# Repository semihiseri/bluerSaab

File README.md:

# bluerSaab
An ESP32 Port of the great BlueSaab projects. What? Yes, I lack creativity.

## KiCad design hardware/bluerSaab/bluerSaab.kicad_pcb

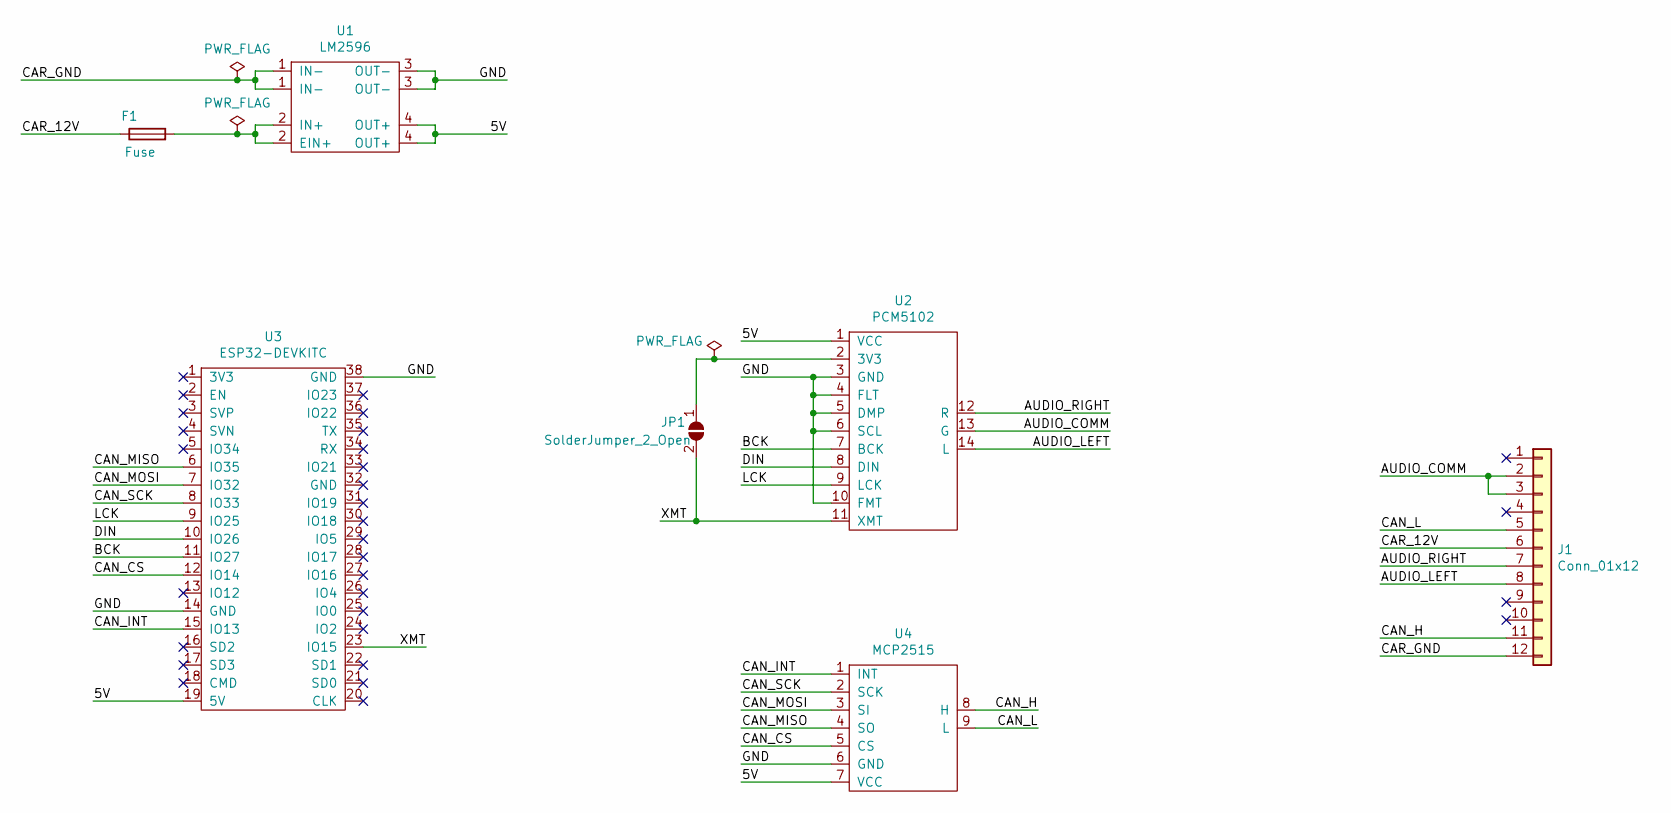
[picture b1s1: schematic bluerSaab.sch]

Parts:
F1: Fuse; Fuseholder_Fuse_TR5_Littlefuse-No560_No460
J1: Conn_01x12; SAAB_CDC
JP1: SolderJumper_2_Open; SolderJumper-2_P1.3mm_Open_TrianglePad1.0x1.5mm
U1: LM2596
U2: PCM5102
U3: ESP32-DEVKITC
U4: MCP2515

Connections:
/5V: U1.4 (OUT+), U2.1 (VCC), U3.19 (5V), U4.7 (VCC)
/AUDIO_COMM: J1.2, J1.3, U2.13 (G)
/AUDIO_LEFT: J1.8, U2.14 (L)
/AUDIO_RIGHT: J1.7, U2.12 (R)
/BCK: U2.7 (BCK), U3.11 (IO27)
/CAN_CS: U3.12 (IO14), U4.5 (CS)
/CAN_H: J1.11, U4.8 (H)
/CAN_INT: U3.15 (IO13), U4.1 (INT)
/CAN_L: J1.5, U4.9 (L)
/CAN_MISO: U3.6 (IO35), U4.4 (SO)
/CAN_MOSI: U3.7 (IO32), U4.3 (SI)
/CAN_SCK: U3.8 (IO33), U4.2 (SCK)
/CAR_12V: F1.1, J1.6
/CAR_GND: J1.12, U1.1 (IN-)
/DIN: U2.8 (DIN), U3.10 (IO26)
/GND: U1.3 (OUT-), U2.3 (GND), U2.4 (FLT), U2.5 (DMP), U2.6 (SCL), U2.10 (FMT), U3.14 (GND), U3.38 (GND), U4.6 (GND)
/LCK: U2.9 (LCK), U3.9 (IO25)
/XMT: JP1.2 (B), U2.11 (XMT), U3.23 (IO15)
unnamed: F1.2, U1.2 (EIN+)
unnamed: JP1.1 (A), U2.2 (3V3)

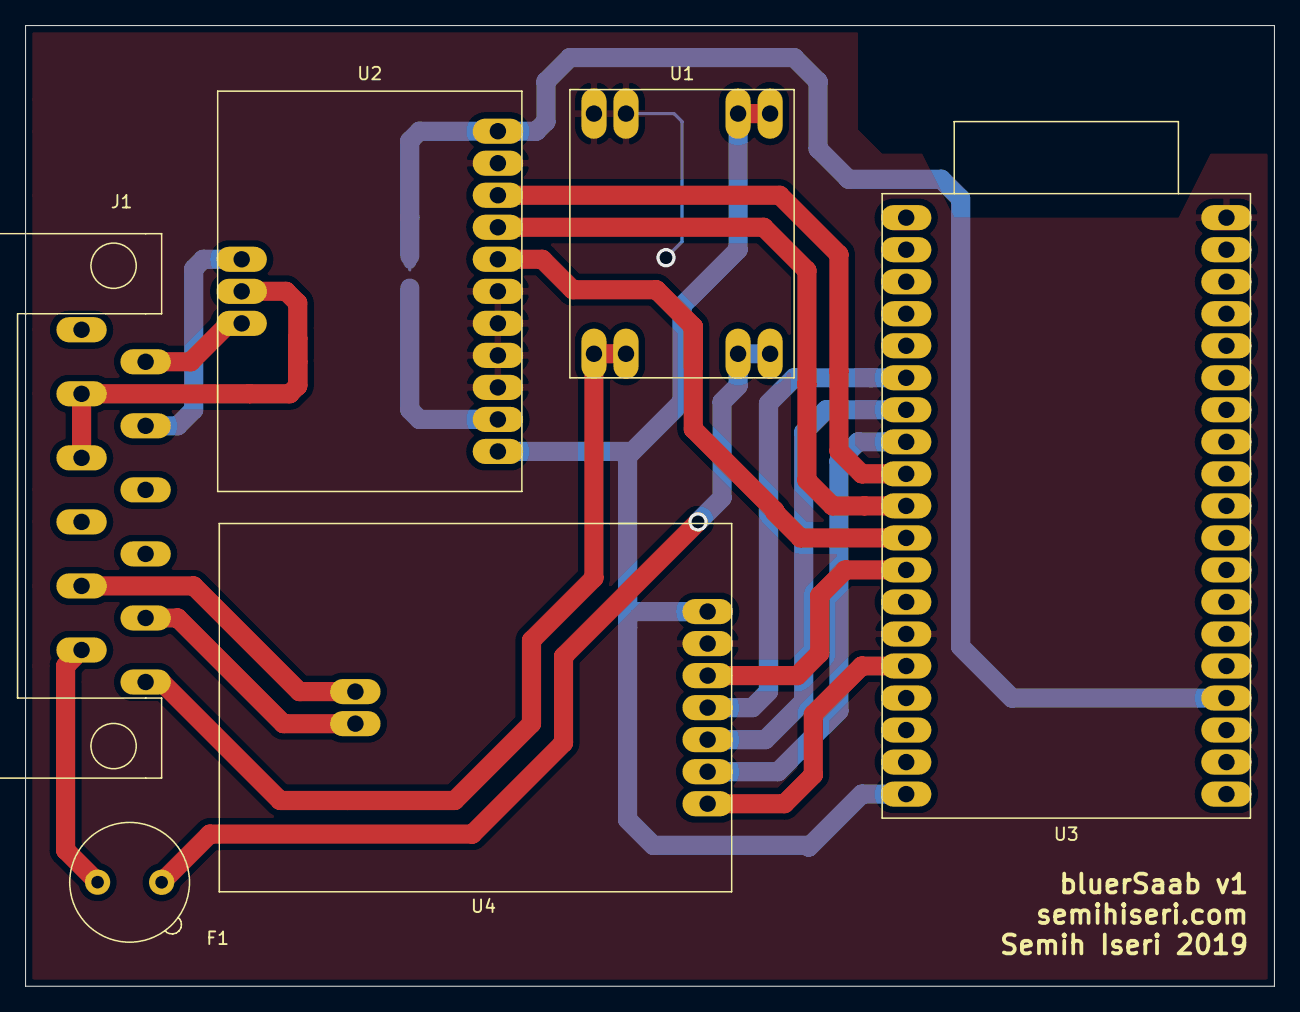
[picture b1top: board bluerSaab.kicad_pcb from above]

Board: 2 copper layers, 99.1 x 76.2 mm, 7 parts (1 on the bottom side), 20 nets.

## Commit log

2019-04-29 .gitignore file for build directory and .old files
2019-04-29 initial commit: mvp with reset & powersave & play
2019-06-16 schematics with xmt
2019-06-16 Fuse added
2019-06-17 footprints added
2019-06-17 Initial layout -missing footprints for conn and fuse
2019-06-17 some tracing done
2019-06-18 Footprints fixed, PCB done
2019-06-18 PCB minified to bring the size below 10x10cm
2019-06-19 Via sizes fixed
